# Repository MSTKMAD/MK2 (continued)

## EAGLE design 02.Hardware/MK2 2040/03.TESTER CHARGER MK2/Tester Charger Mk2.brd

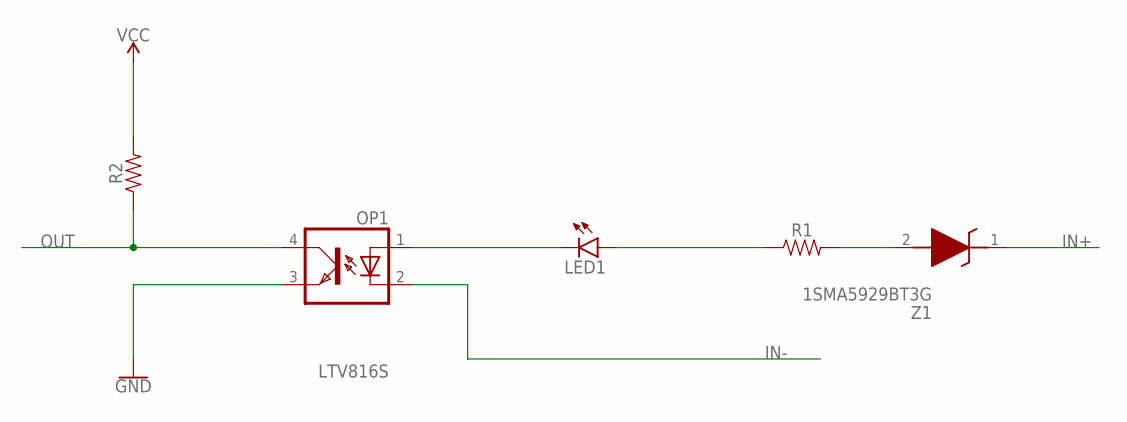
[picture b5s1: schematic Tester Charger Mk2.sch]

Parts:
LED1: LED3MM
OP1: LTV816S; SMD4
R1, R2: 0805
Z1: 1SMA5929BT3G; DIOM5226X220N

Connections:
GND: OP1.3 (EMIT)
IN+: Z1.1 (K)
IN-: OP1.2 (C)
unnamed: LED1.K (C), OP1.1 (A)
unnamed: R1.2, Z1.2 (A)
unnamed: LED1.A, R1.1
OUT: OP1.4 (COL), R2.1
VCC: R2.2

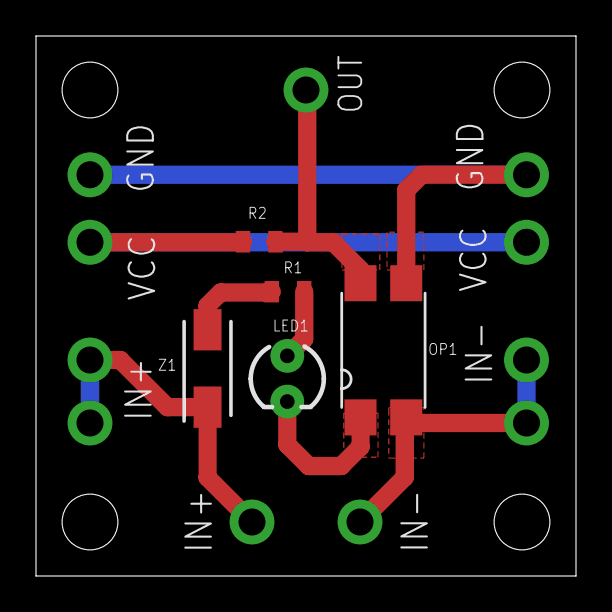
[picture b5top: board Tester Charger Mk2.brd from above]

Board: 2 copper layers, 30.0 x 30.0 mm, 5 parts (0 on the bottom side), 4 nets.

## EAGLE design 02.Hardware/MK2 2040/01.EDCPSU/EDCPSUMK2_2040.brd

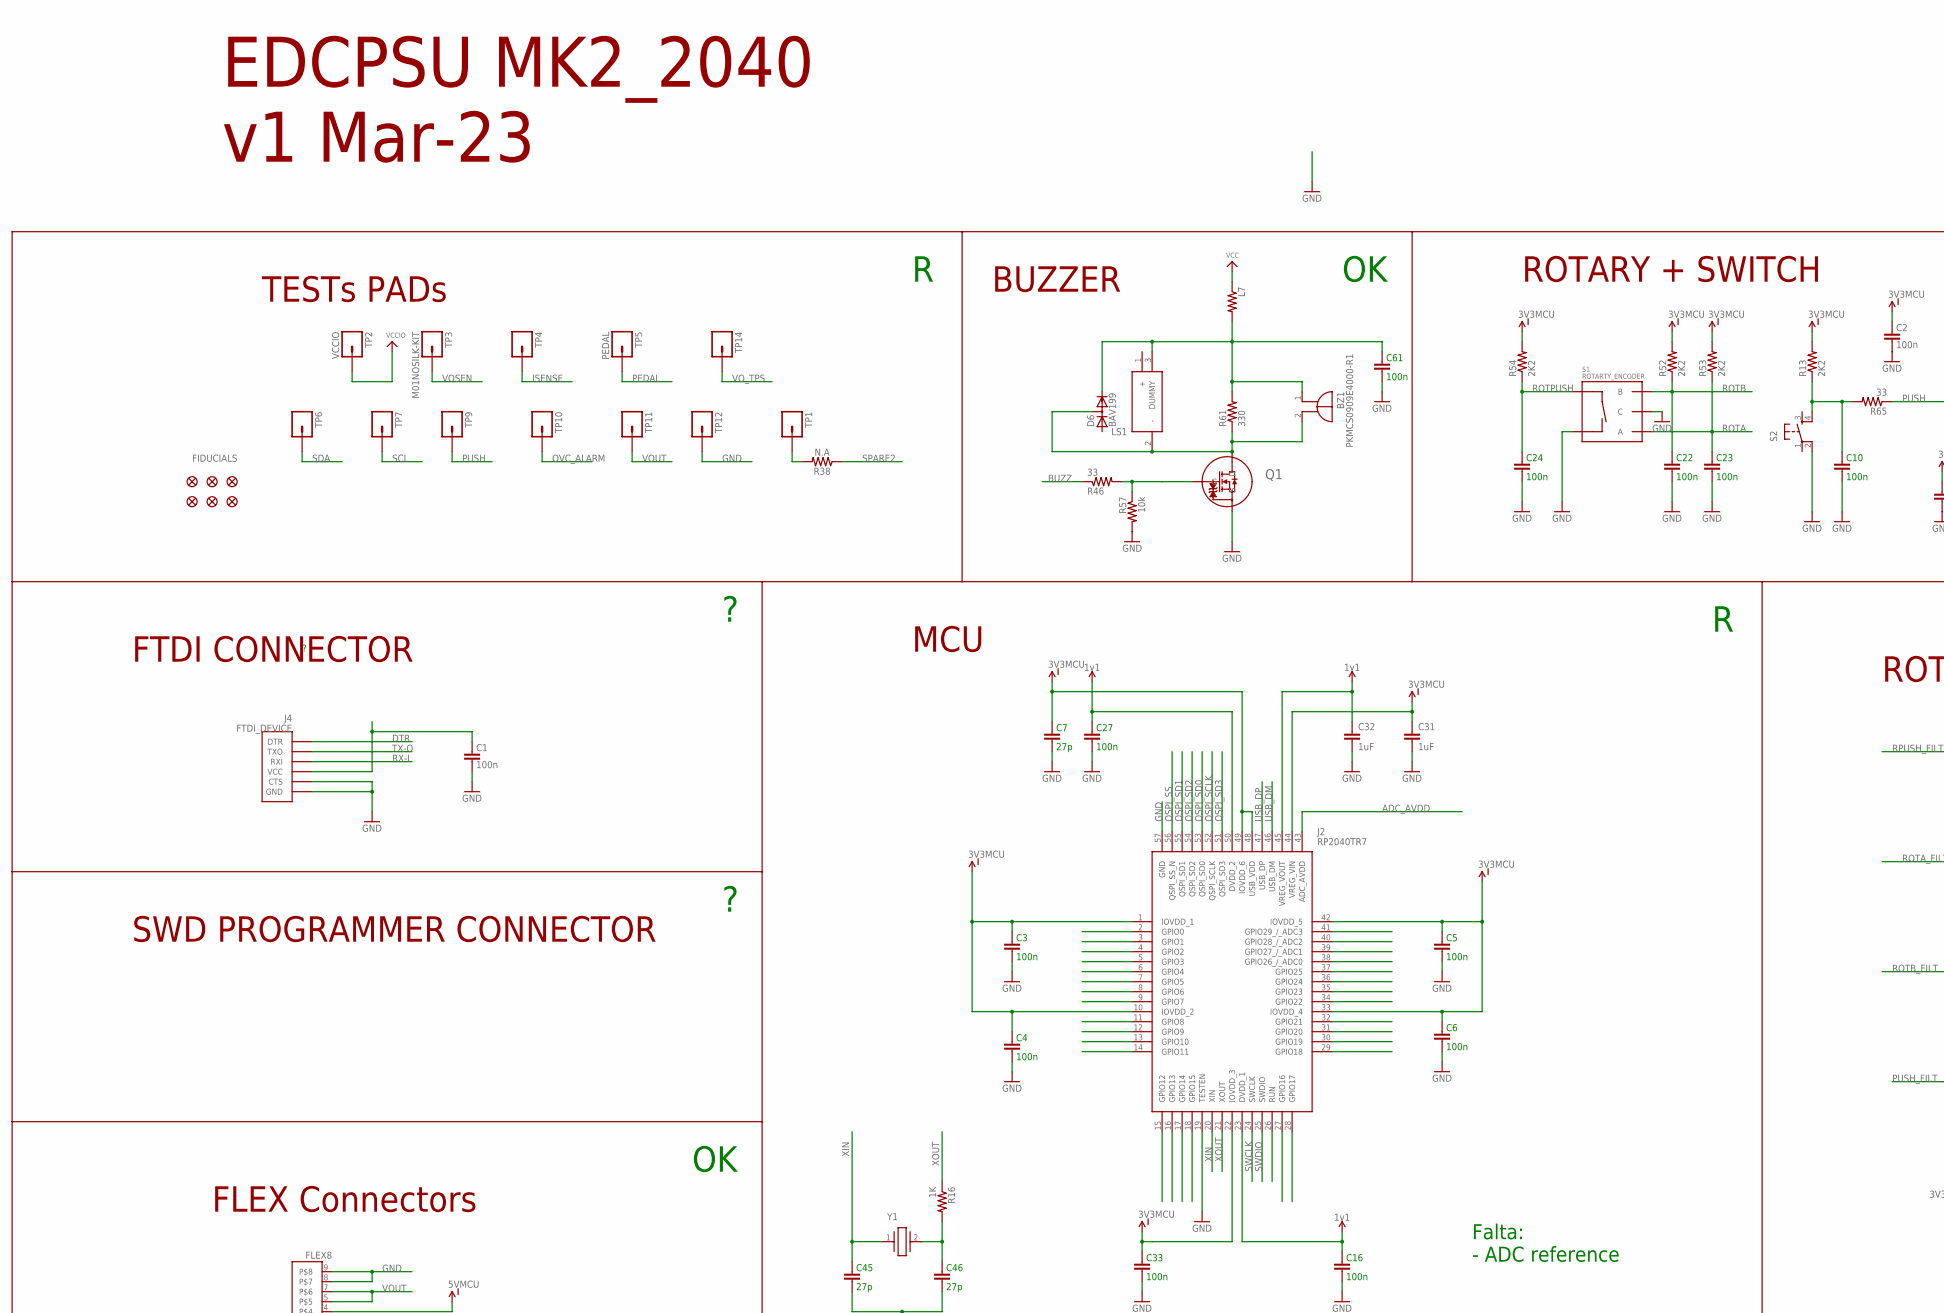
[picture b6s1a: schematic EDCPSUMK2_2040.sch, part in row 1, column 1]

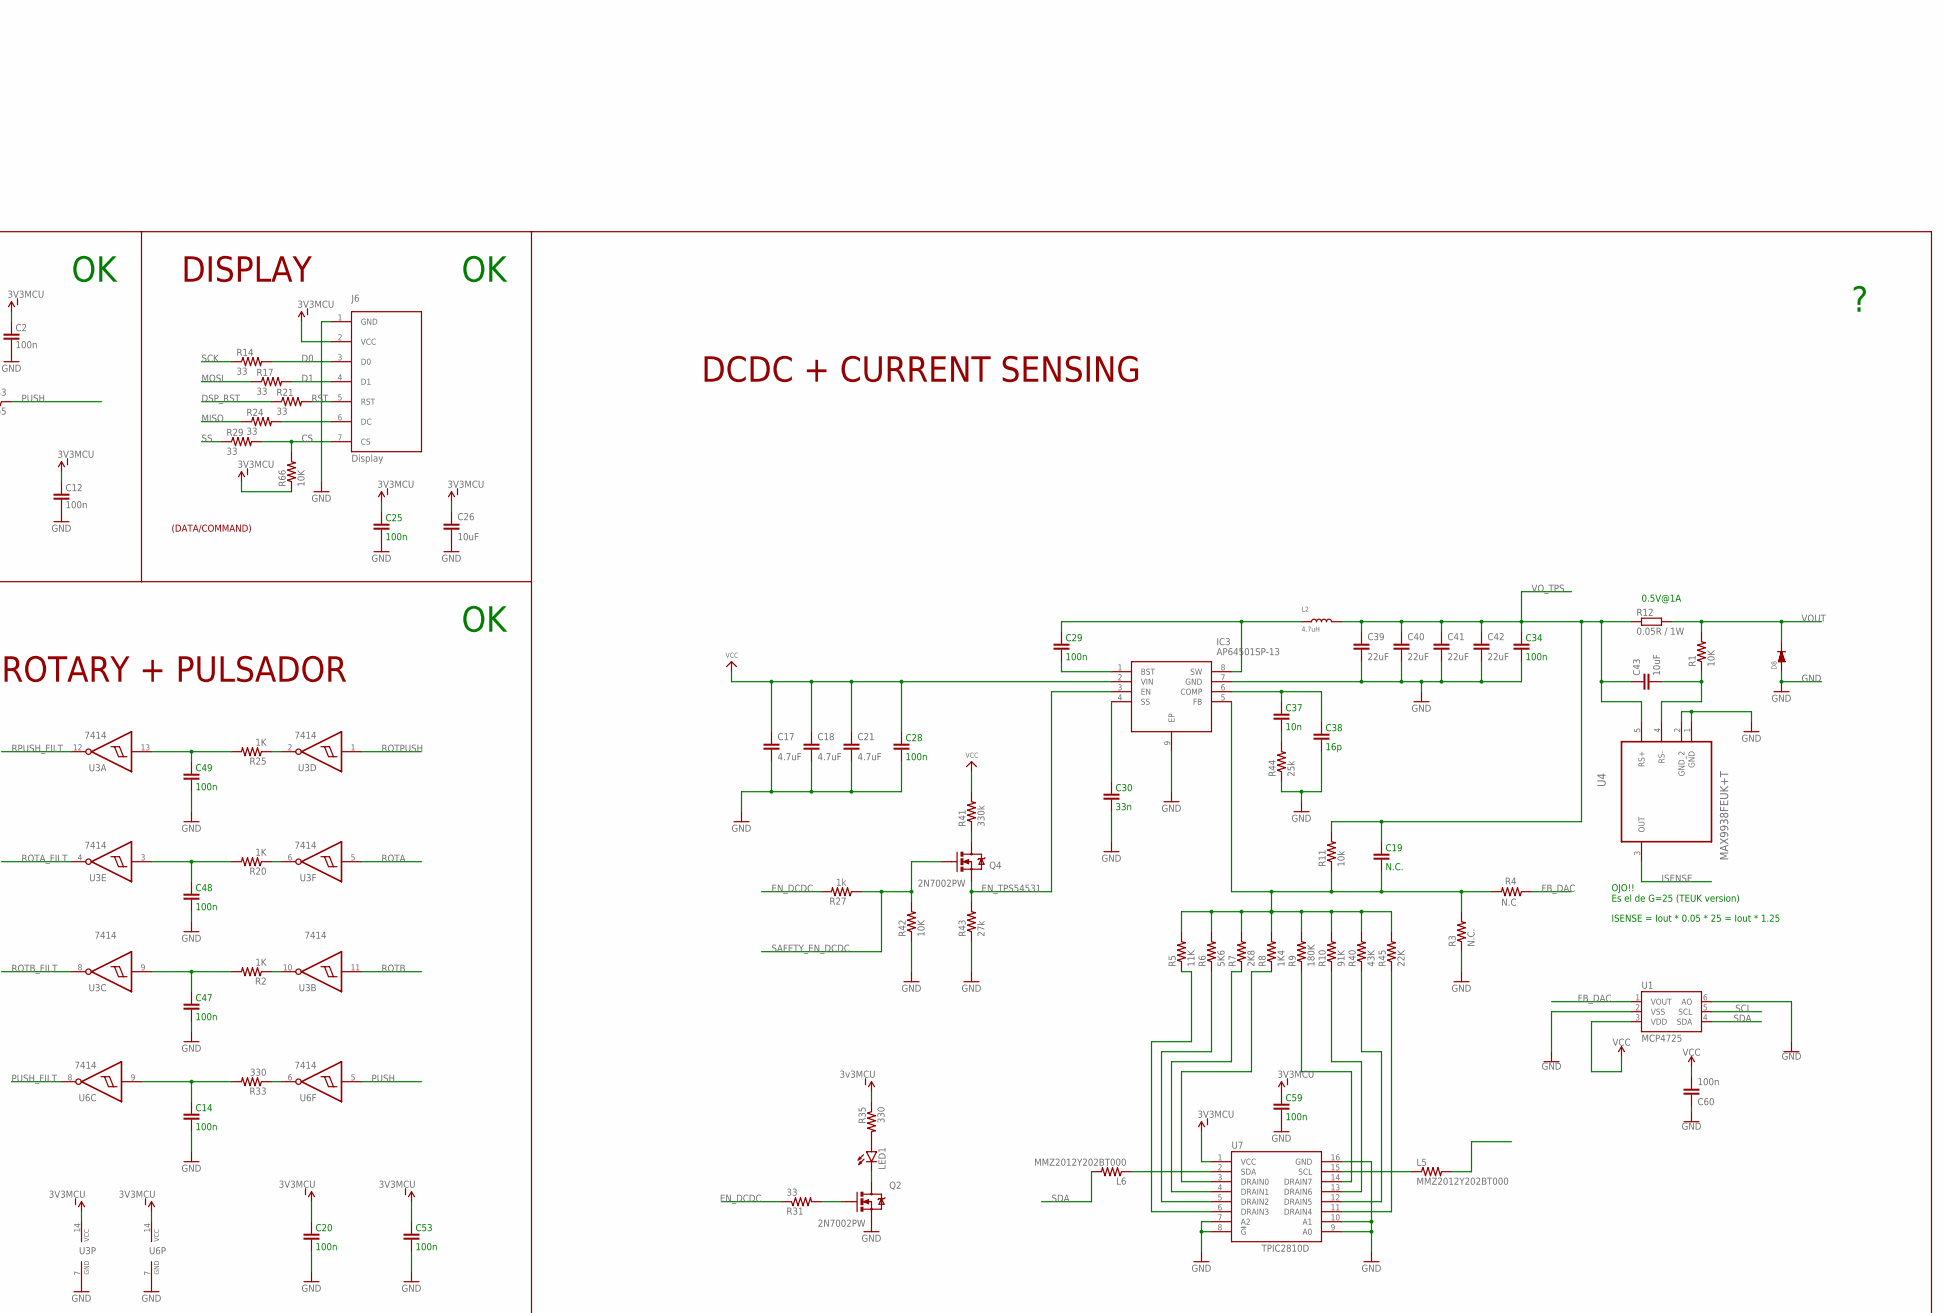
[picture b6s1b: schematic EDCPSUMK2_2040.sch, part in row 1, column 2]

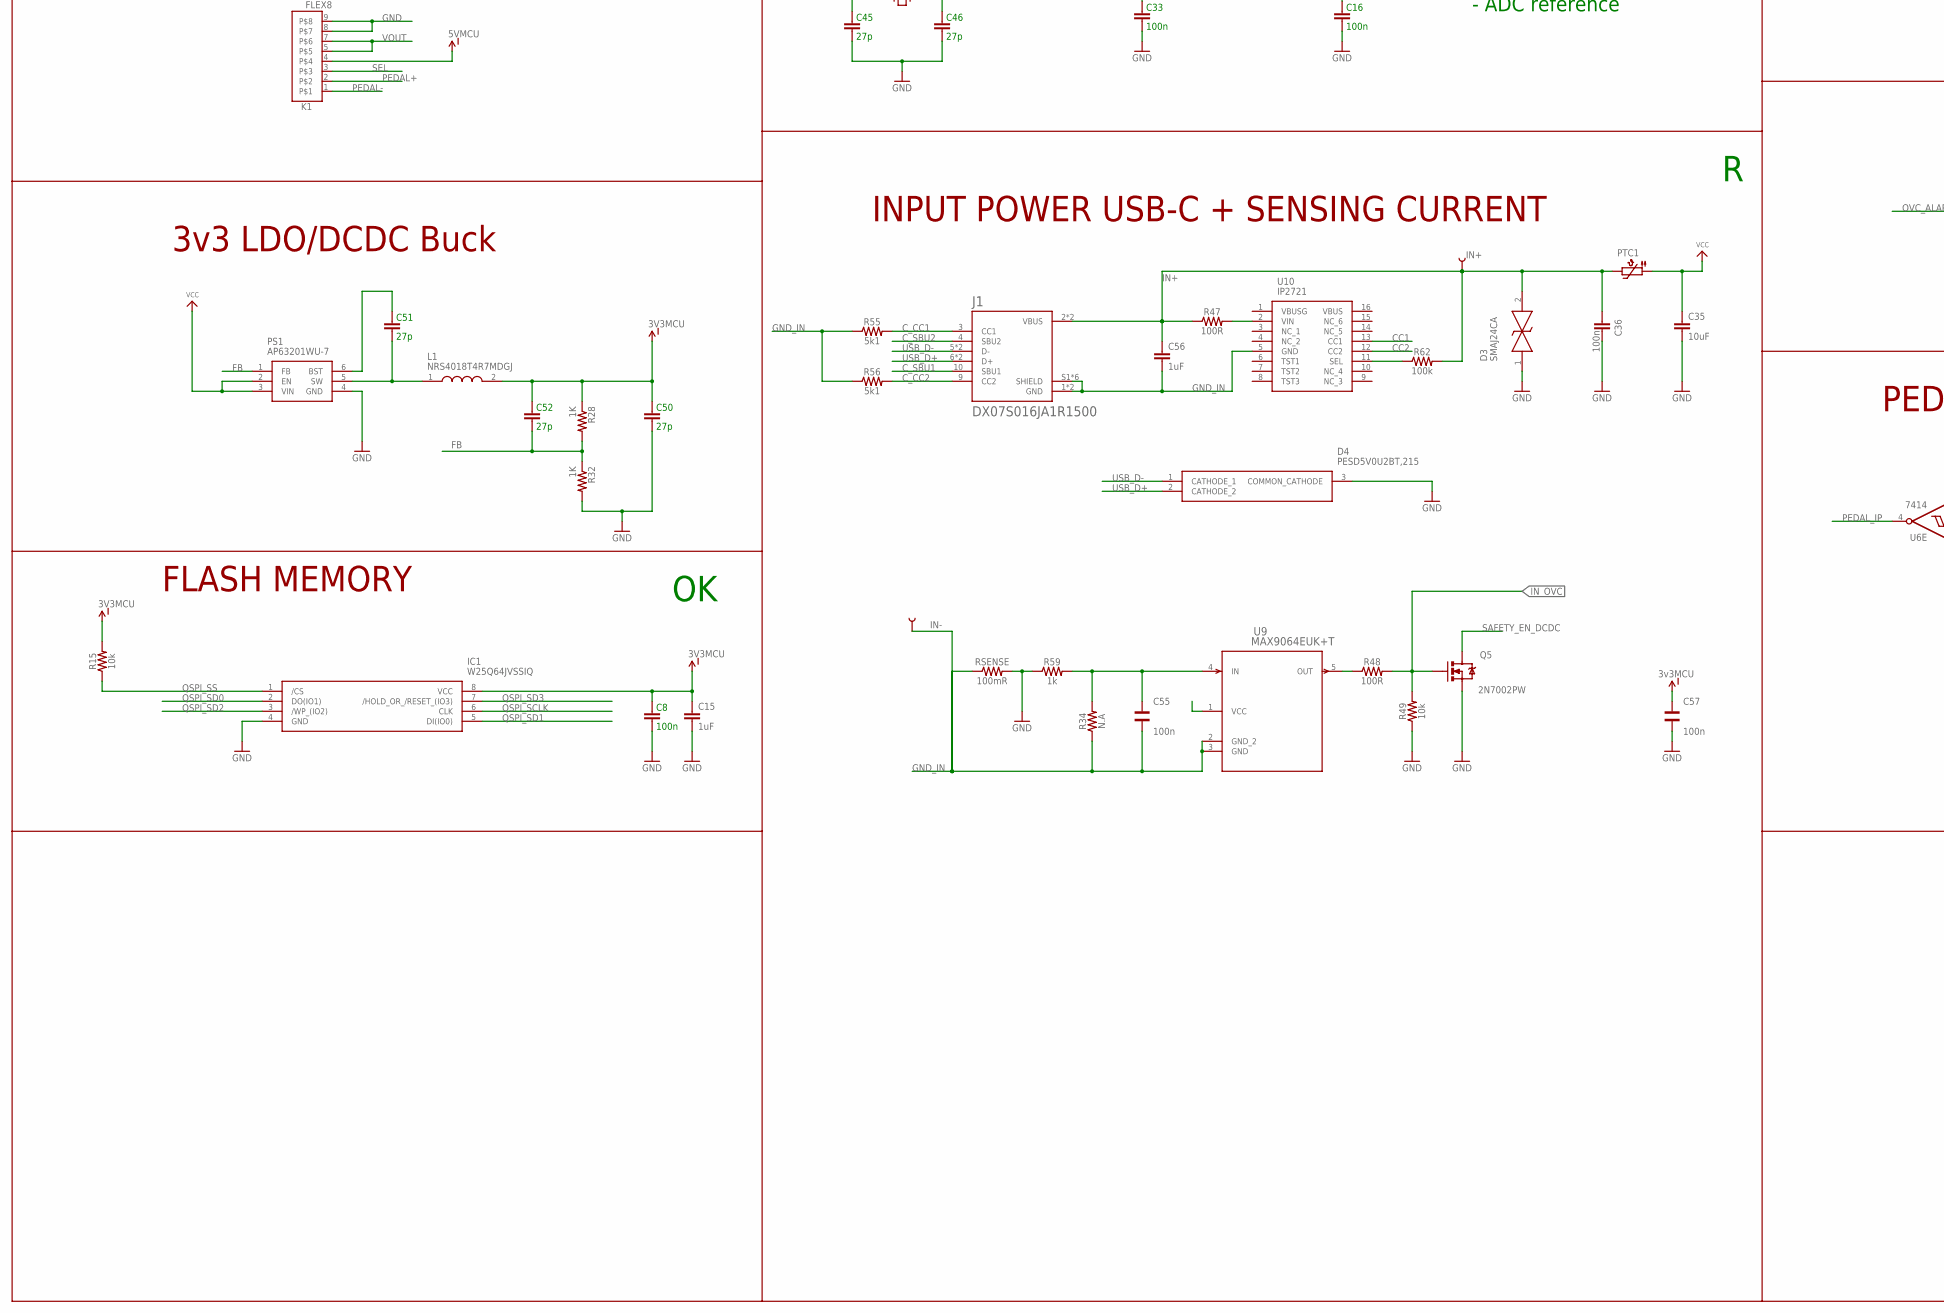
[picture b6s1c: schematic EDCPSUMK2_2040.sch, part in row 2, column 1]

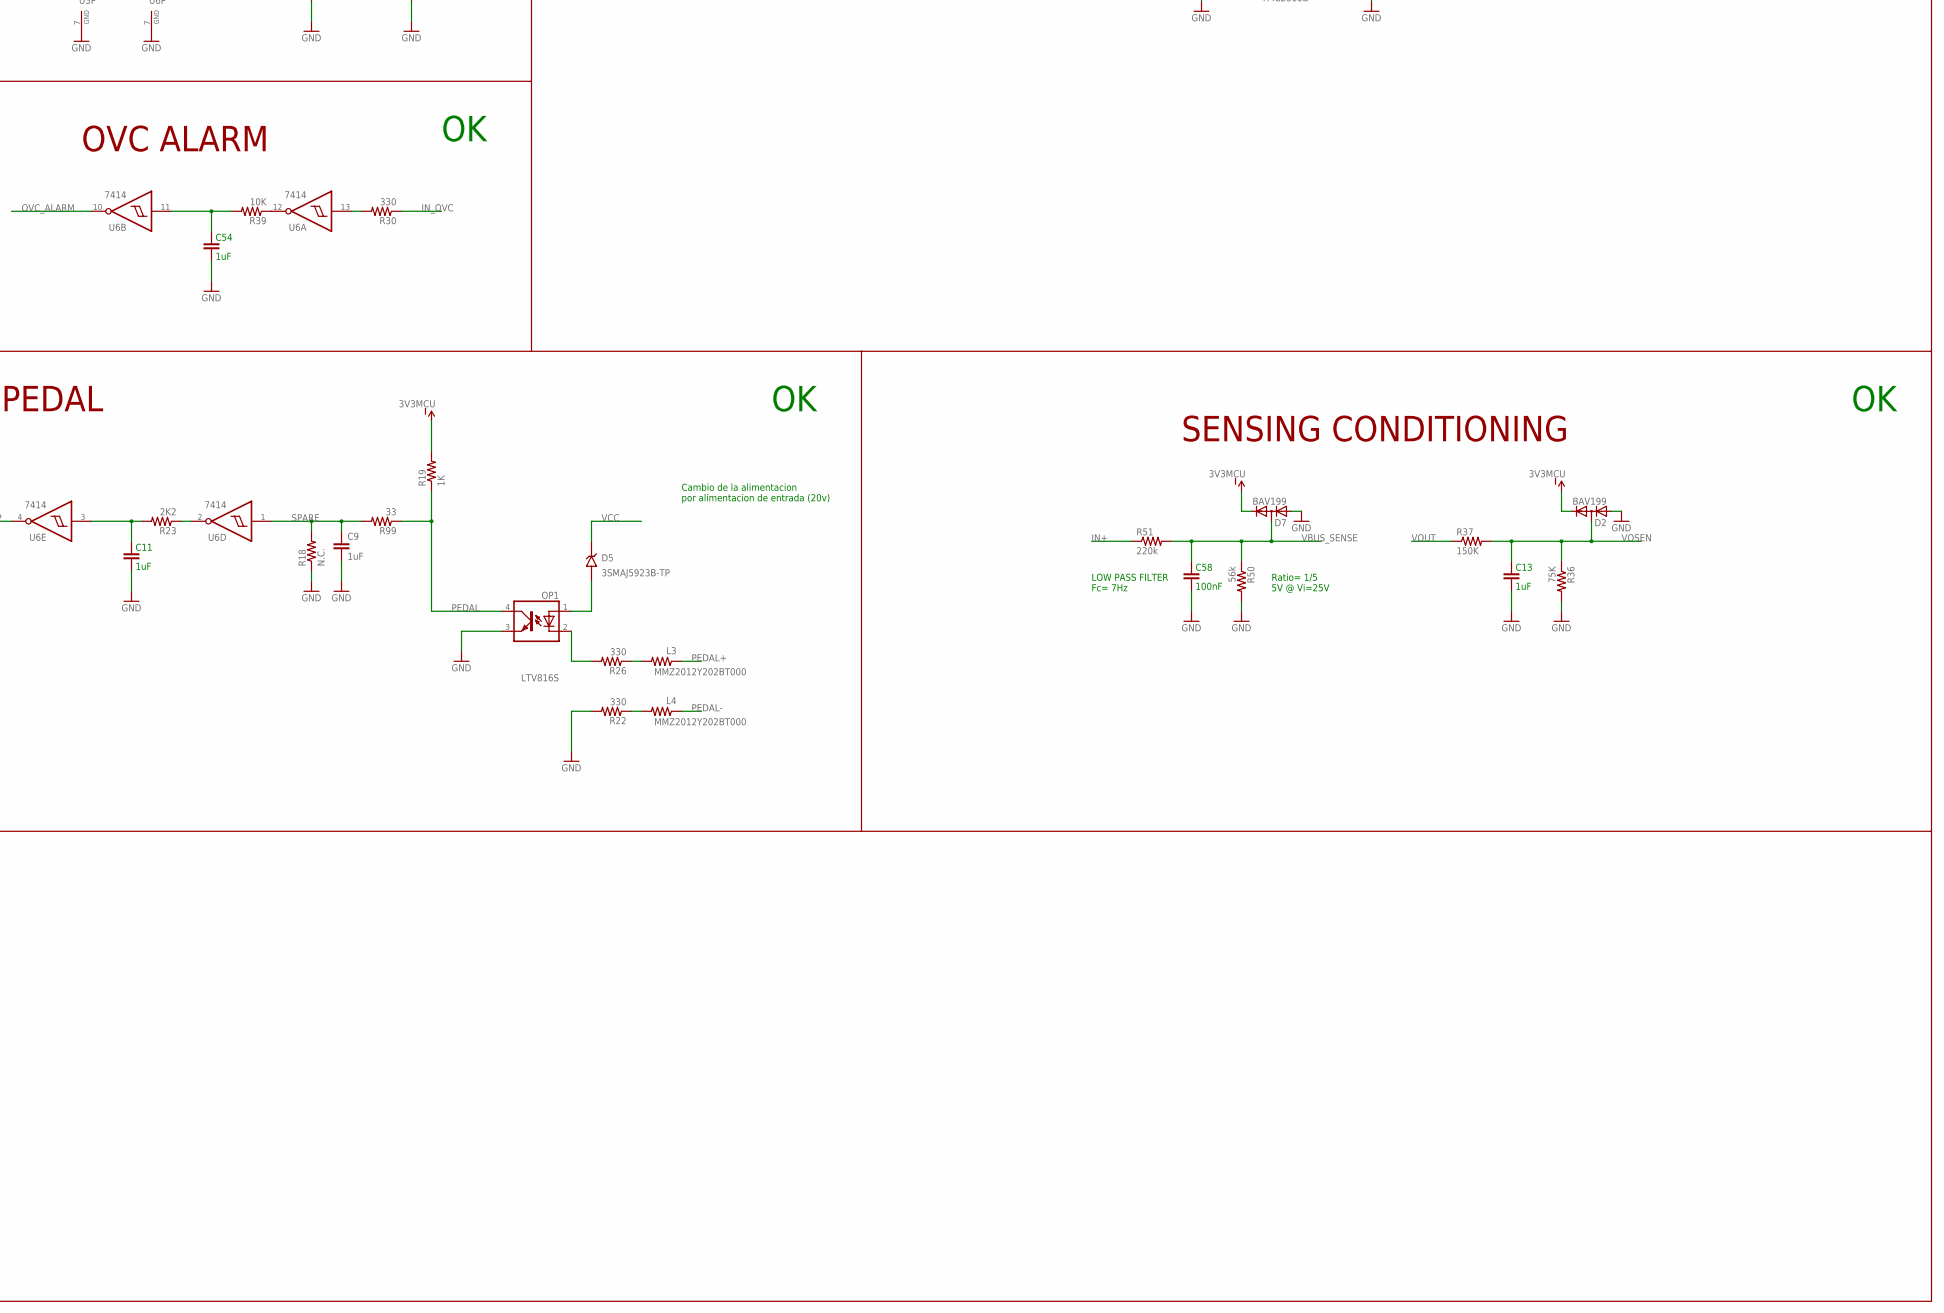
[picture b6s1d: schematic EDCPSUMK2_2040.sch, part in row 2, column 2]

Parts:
BZ1: PKMCS0909E4000-R1; PKMCS0909
C1, C2, C3, C4, C5, C6, C8, C10, C12, C14, C16, C20, C22, C23, C24, C25, C27, C28, C29, C33, C34, C36, C47, C48, C49, C53, C59, C61: 100n; 0805
C7, C45, C46, C50, C51, C52: 27p; 0805
C9, C15, C31, C32, C56: 1uF; 1206
C11, C13, C54: 1uF; 0805
C17, C18, C21: 4.7uF; 1210
C19: N.C.; 0805
C26, C35, C43: 10uF; 1206
C30: 33n; 0805
C37: 10n; 0805
C38: 16p; 0805
C39, C40, C41, C42: 22uF; 1210
C55, C57: 100n; WCAP-CSGP_1206
C58: 100nF; 0805
C60: 100n; C0805
D2, D6, D7: BAV199; SOT23
D3: SMAJ24CA; DIONM5127X229N
D4: PESD5V0U2BT,215; SOT95P230X110-3N
D5: 3SMAJ5923B-TP; DIOM4325X244N
D8: RB060M-60TR; SMADIODE
FID1, FID2, FID3, FID4, FID5, FID6: FIDUCIAL1X2; FIDUCIAL-1X2
IC1: W25Q64JVSSIQ; SOIC127P790X216-8N
IC3: AP64501SP-13; SOIC127P600X163-9N
IN+: TEST-POINT3; PAD.03X.03
IN-: TEST-POINT3; PAD.03X.03
J1: DX07S016JA1R1500; JAE_DX07S016JA1R1500
J2: RP2040TR7
J4: FTDI_DEVICE; FTDI_DEVICE_SIDE
J6: Display; OLED_LCD
K1: FLEX8
L1: NRS4018T4R7MDGJ; NRS4018T100MDGJ
L2: 4.7uH; WE-LHMI
L3, L4, L5, L6, L7: MMZ2012Y202BT000; 0805
LED1: LED3MM
LS1: SMT-0540-S-R; SMT0540SR
OP1: LTV816S; SMD4
PS1: AP63201WU-7; SOT95P280X100-6N
PTC1: 2A NOM / 3.5A LIM; 1812L
Q1: PJA3416AE_R1_00001; SOT23_PJA3416_PNJ
Q2, Q4, Q5: 2N7002PW; SOT323
R1, R39, R42, R66: 10K; 0805
R2, R16, R19, R20, R25, R28, R32: 1K; 0805
R3, R18: N.C.; 0805
R4: N.C; 0805
R5: 11K; 0805
R6: 5K6; 0805
R7: 2K8; 0805
R8: 1K4; 0805
R9: 180K; 0805
R10: 91K; 0805
R11, R57: 10k; 0805
R12: 0.05R / 1W; R2512
R13, R23, R52, R53, R54: 2K2; 0805
R14, R17, R21, R24, R29, R31, R46, R65, R99: 33; 0805
R15, R49: 10k; 0603
R22, R26: 330; 1206
R27: 1k; 0805
R30, R33, R35, R61: 330; 0805
R34, R38: N.A; 0603
R36: 75K; 0805
R37: 150K; 0805
R40: 43K; 0805
R41: 330k; 0805
R43: 27k; 0805
R44: 25k; 0805
R45: 22K; 0805
R47, R48: 100R; 0603
R50: 56k; 0603
R51: 220k; 0603
R55, R56: 5k1; 0603
R59: 1k; 0603
R62: 100k; 0603
RSENSE: 100mR; 1206
S1: ROTARTY_ENCODER; ROTARY_ENC_PLAIN
S2: TAC_SWITCH_KSC931G-SMD; TAC_SW_SMD_KSC931G
TP1, TP4, TP6, TP7, TP9, TP10, TP11, TP12, TP14: M01POGOPIN_HOLE_LARGE; 1X01_POGOPIN_HOLE_LARGE
TP2: VCCIO; 1X01_POGOPIN_HOLE_LARGE
TP3: M01NOSILK-KIT; 1X01NS-KIT
TP5: PEDAL; 1X01_POGOPIN_HOLE_LARGE
U1: MCP4725; SOT23-6
U3, U6: 7414; TSSOP14
U4: MAX9938FEUK+T; SOT95P280X145-5N
U7: TPIC2810D; SO16
U9: MAX9064EUK+T; 21-0057F_MXM
U10: IP2721; SOP65P640X120-16N
Y1: ABLS-12.000MHZ-B4-T; ABLS

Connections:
ADC_AVDD: J2.43 (ADC_AVDD)
BUZZ: R46.1
CC1: U10.13 (CC1)
CC2: U10.12 (CC2)
CS: J6.7 (CS), R29.2, R66.2
C_CC1: J1.3 (CC1), R55.2
C_CC2: J1.9 (CC2), R56.2
C_SBU1: J1.10 (SBU1)
C_SBU2: J1.4 (SBU2)
D0: J6.3 (D0), R14.2
D1: J6.4 (D1), R17.2
DSP_RST: R21.1
DTR: J4.P$1 (DTR)
EN_DCDC: R27.2, R31.1
EN_TPS54531: IC3.3 (EN), Q4.2 (S), R43.2
FB: C52.1, PS1.1 (FB), R28.2, R32.1
FB_DAC: R4.1, U1.1 (VOUT)
GND: C1.1, C2.1, C3.1, C4.1, C5.1, C6.1, C7.1, C8.1, C9.2, C10.1, C11.1, C12.1, C13.1, C14.1, C15.2, C16.1, C17.2, C18.2, C20.1, C21.2, C22.1, C23.1, C24.1, C25.1, C26.2, C27.1, C28.1, C30.1, C31.2, C32.2, C33.1, C34.1, C35.2, C36.1, C38.1, C39.2, C40.2, C41.2, C42.2, C45.1, C46.1, C47.1, C48.1, C49.1, C50.1, C53.1, C54.1, C57.1, C58.1, C59.1, C60.1, C61.1, D2.1 (A), D3.1, D4.3 (COMMON_CATHODE), D7.1 (A), D8.A, IC1.4 (GND), IC3.7 (GND), IC3.9 (EP), J2.19 (TESTEN), J2.57 (GND), J4.P$5 (CTS), J4.P$6 (GND), J6.1 (GND), K1.8, K1.9, OP1.3 (EMIT), PS1.4 (GND), Q1.2 (S), Q2.2 (S), Q5.2 (S), R3.1, R18.1, R22.2, R32.2, R36.2, R42.1, R43.1, R44.1, R49.1, R50.2, R57.2, R59.1, RSENSE.2, S1.C, S1.SW-, S2.2, TP12.1, U1.2 (VSS), U1.6 (AO), U3.7 (GND), U4.1 (GND), U4.2 (GND_2), U6.7 (GND), U7.7 (A2), U7.8 (!G), U7.9 (A0), U7.10 (A1), U7.16 (GND); also elsewhere on the board
GND_IN: C55.1, C56.2, IN-.P$1, J1.1 (GND), J1.12 (GND), J1.S1 (SHIELD), J1.S2 (SHIELD), J1.S3 (SHIELD), J1.S4 (SHIELD), J1.S5 (SHIELD), J1.S6 (SHIELD), R34.1, R55.1, R56.1, RSENSE.1, U9.2 (GND_2), U9.3 (GND), U10.5 (GND)
IN+: C36.2, C56.1, D3.2, IN+.P$1, J1.2 (VBUS), J1.11 (VBUS), PTC1.2, R47.1, R51.1, R62.2
ISENSE: TP4.1, U4.3 (OUT)
MISO: R24.1
MOSI: R17.1
unnamed: R5.1, U7.6 (DRAIN3)
unnamed: R6.1, U7.5 (DRAIN2)
unnamed: R7.1, U7.4 (DRAIN1)
unnamed: R8.1, U7.3 (DRAIN0)
unnamed: J6.6 (DC), R24.2
unnamed: R9.1, U7.14 (DRAIN7)
unnamed: R10.1, U7.13 (DRAIN6)
unnamed: R40.1, U7.12 (DRAIN5)
unnamed: C43.2, R1.1, U4.4 (RS-)
unnamed: LED1.A, R35.2
unnamed: LED1.K (C), Q2.3 (D)
unnamed: R33.1, U6.6 (O)
unnamed 35: R30.2, U6.13 (I); also elsewhere on the board
unnamed: R39.1, U6.12 (O)
unnamed: R45.1, U7.11 (DRAIN4)
unnamed: C10.2, R13.1, R65.2, S2.4
unnamed: C47.2, R2.2, U3.9 (I)
unnamed: D5.A, OP1.1 (A)
unnamed: Q2.1 (G), R31.2
unnamed: R2.1, U3.10 (O)
unnamed: R20.1, U3.6 (O)
unnamed: R25.1, U3.2 (O)
unnamed: C49.2, R25.2, U3.13 (I)
unnamed: C48.2, R20.2, U3.3 (I)
unnamed: C11.2, R23.2, U6.3 (I)
unnamed: C1.2, J4.P$4 (VCC)
unnamed: R23.1, U6.2 (O)
unnamed: Q4.3 (D), R41.1
unnamed: C14.2, R33.2, U6.9 (I)
unnamed: R38.2, TP1.1
unnamed: C54.2, R39.2, U6.11 (I)
unnamed: L6.1, U7.2 (SDA)
unnamed: OP1.2 (C), R26.2
unnamed: L3.2, R26.1
unnamed: C30.2, IC3.4 (SS)
unnamed: R62.1, U10.11 (SEL)
unnamed: L4.2, R22.1
unnamed: C29.1, IC3.1 (BST)
unnamed: C19.1, IC3.5 (FB), R3.2, R4.2, R5.2, R6.2, R7.2, R8.2, R9.2, R10.2, R11.1, R40.2, R45.2
unnamed: R47.2, U10.2 (VIN)
unnamed: C29.2, IC3.8 (SW), L2.1
unnamed: C37.2, C38.2, IC3.6 (COMP)
unnamed: C37.1, R44.2
unnamed: L5.1, U7.15 (SCL)
unnamed: C51.2, PS1.6 (BST)
unnamed: R48.1, U9.5 (OUT)
unnamed: C55.2, R34.2, R59.2, U9.4 (IN)
unnamed: C46.2, R16.2, Y1.2
unnamed: Q1.1 (G), R46.2, R57.1
unnamed: BZ1.2 (-), D6.3 (AC), LS1.2 (-), Q1.3 (D), R61.1
unnamed: C51.1, L1.1, PS1.5 (SW)
PEDAL: OP1.4 (COL), R19.1, R99.1, TP5.1
PEDAL+: K1.2, L3.1
PEDAL-: K1.1, L4.1
PEDAL_IP: U6.4 (O)
PUSH: R65.1, TP9.1, U6.5 (I)
PUSH_FILT: U6.8 (O)
QSPI_SCLK: IC1.6 (CLK), J2.52 (QSPI_SCLK)
QSPI_SD0: IC1.2 (DO(IO1)), J2.53 (QSPI_SD0)
QSPI_SD1: IC1.5 (DI(IO0)), J2.55 (QSPI_SD1)
QSPI_SD2: IC1.3 (/WP_(IO2)), J2.54 (QSPI_SD2)
QSPI_SD3: IC1.7 (/HOLD_OR_/RESET_(IO3)), J2.51 (QSPI_SD3)
QSPI_SS: IC1.1 (/CS), J2.56 (QSPI_SS_N), R15.1
ROTA: C23.2, R53.1, S1.A, U3.5 (I)
ROTA_FILT: U3.4 (O)
ROTB: C22.2, R52.1, S1.B, U3.11 (I)
ROTB_FILT: U3.8 (O)
ROTPUSH: C24.2, R54.1, S1.SW+, U3.1 (I)
RPUSH_FILT: U3.12 (O)
RST: J6.5 (RST), R21.2
RX-I: J4.P$3 (RXI)
SAFETY_EN_DCDC: Q4.1 (G), Q5.3 (D), R27.1, R42.2
SCK: R14.1
SCL: TP7.1, U1.5 (SCL)
SCL1: L5.2
SDA: L6.2, TP6.1, U1.4 (SDA)
SEL: K1.3
SPARE: C9.1, R18.2, R99.2, U6.1 (I)
SPARE2: R38.1
SS: R29.1
SWCLK: J2.24 (SWCLK)
SWDIO: J2.25 (SWDIO)
TX-O: J4.P$2 (TXO)
USB_D+: D4.2 (CATHODE_2), J1.6 (D+), J1.7 (D+)
USB_D-: D4.1 (CATHODE_1), J1.5 (D-), J1.8 (D-)
USB_DM: J2.46 (USB_DM)
USB_DP: J2.47 (USB_DP)
VBUS_SENSE: C58.2, D7.3 (AC), R50.1, R51.2
VCC: C17.1, C18.1, C21.1, C28.2, C35.1, C60.2, D5.C (K), IC3.2 (VIN), L7.1, PS1.2 (EN), PS1.3 (VIN), PTC1.1, R41.2, U1.3 (VDD); also elsewhere on the board
VCC-ISO: C2.2, C3.2, C4.2, C5.2, C6.2, C7.2, C8.2, C12.2, C15.1, C20.2, C25.2, C26.1, C31.1, C33.2, C50.2, C52.2, C53.2, C57.2, C59.2, D2.2 (C), D7.2 (C), IC1.8 (VCC), J2.1 (IOVDD_1), J2.10 (IOVDD_2), J2.22 (IOVDD_3), J2.33 (IOVDD_4), J2.42 (IOVDD_5), J2.44 (VREG_VIN), J2.48 (USB_VDD), J2.49 (IOVDD_6), J6.2 (VCC), K1.4, L1.2, R13.2, R15.2, R19.2, R28.1, R35.1, R52.2, R53.2, R54.2, R66.1, U3.14 (VCC), U6.14 (VCC), U7.1 (VCC); also elsewhere on the board
VCCA: C16.2, C27.2, C32.1, J2.23 (DVDD_1), J2.45 (VREG_VOUT), J2.50 (DVDD_2)
VCCIO: TP2.1
VIN_ALARM: TP10.1, U6.10 (O)
VOSEN: C13.2, D2.3 (AC), R36.1, R37.2, TP3.1
VOUT: D8.C (K), K1.5, K1.7, R1.2, R12.2, R37.1, TP11.1
VO_TPS: C19.2, C34.2, C39.1, C40.1, C41.1, C42.1, C43.1, L2.2, R11.2, R12.1, TP14.1, U4.5 (RS+)
XIN: C45.2, J2.20 (XIN), Y1.1
XOUT: J2.21 (XOUT), R16.1

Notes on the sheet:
0.5V@1A
SENSING CONDITIONING
MCU
EDCPSU MK2_2040 v1 Mar-23
(DATA/COMMAND)
BUZZER
ROTARY + SWITCH
DISPLAY
FIDUCIALS
OJO!! Es el de G=25 (TEUK version)
ISENSE = Iout * 0.05 * 25 = Iout * 1.25
FLEX Connectors
Ratio= 1/5 5V @ Vi=25V
LOW PASS FILTER Fc= 7Hz
PEDAL
ROTARY + PULSADOR
OVC ALARM
DCDC + CURRENT SENSING
3v3 LDO/DCDC Buck
TESTs PADs
INPUT POWER USB-C + SENSING CURRENT
FTDI CONNECTOR
SWD PROGRAMMER CONNECTOR
Cambio de la alimentacion por alimentacion de entrada (20v)
Falta: - ADC reference
FLASH MEMORY

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
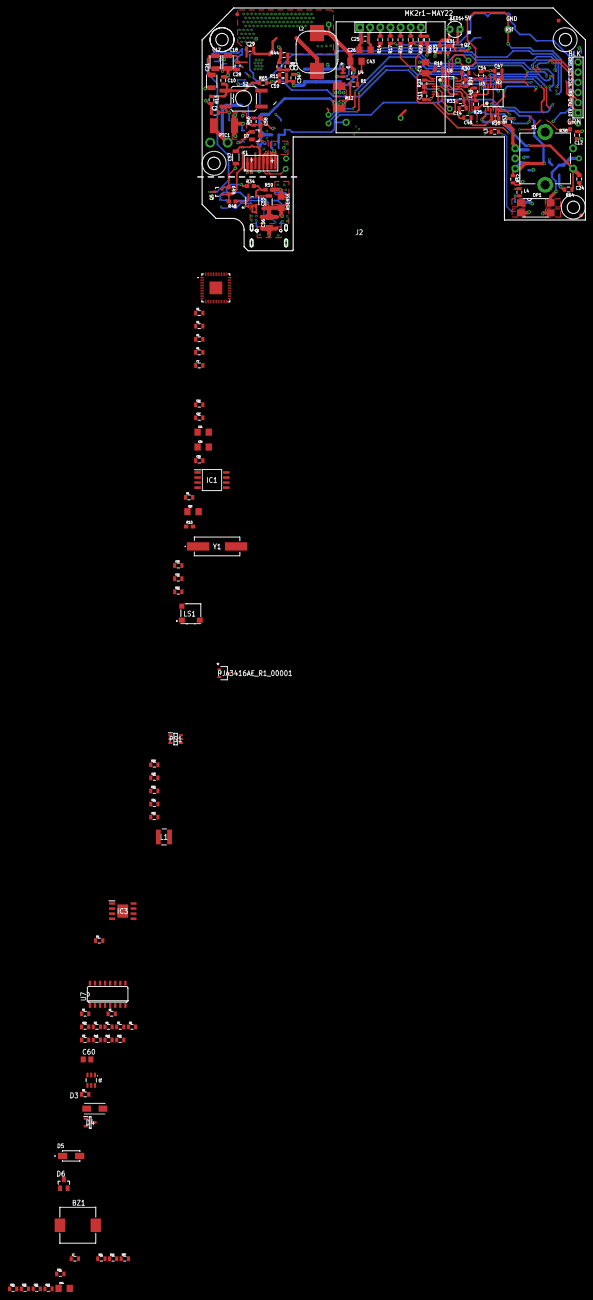
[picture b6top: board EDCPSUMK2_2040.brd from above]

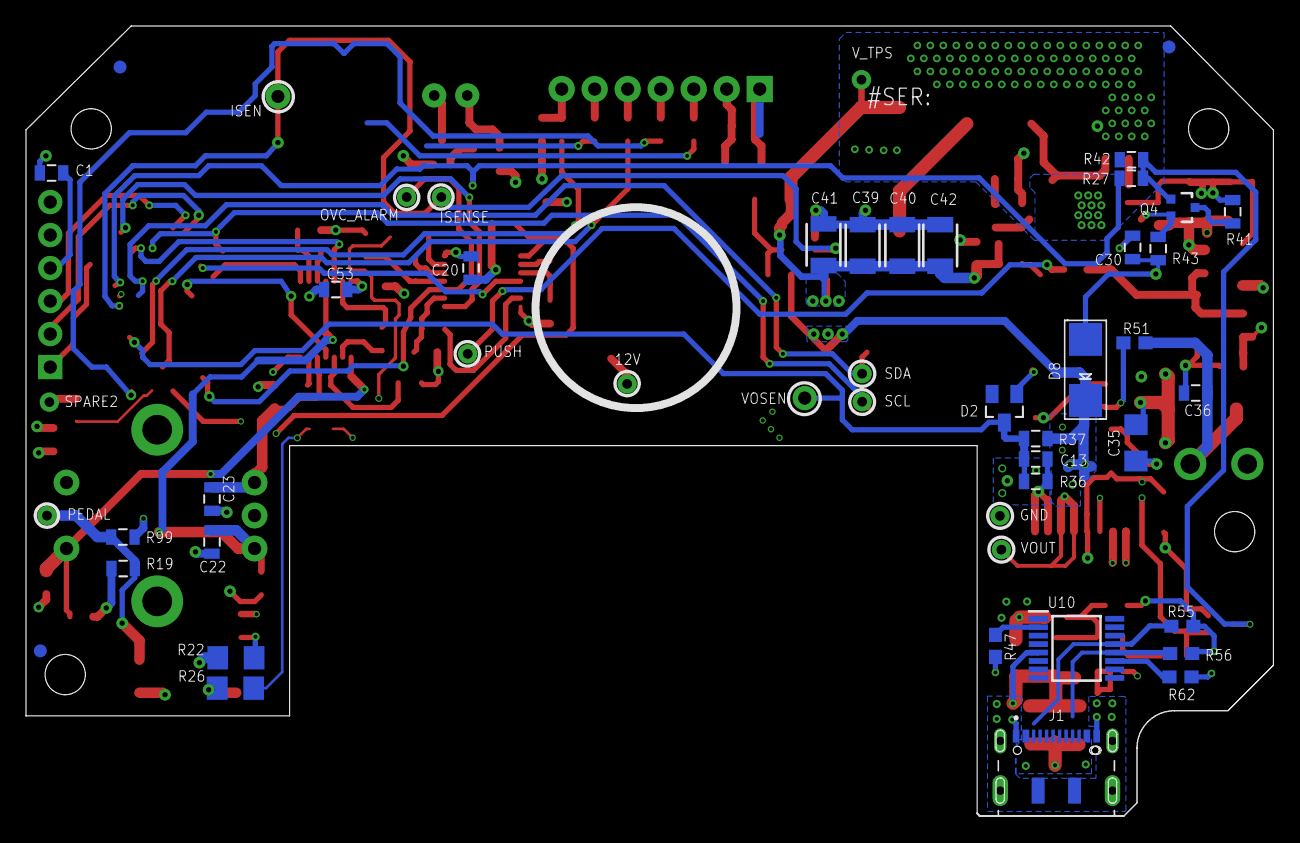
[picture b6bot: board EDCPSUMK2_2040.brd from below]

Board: 4 copper layers, 96.0 x 60.8 mm, 190 parts (36 on the bottom side), 97 nets.

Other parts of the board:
C44: 10uF; 1206
C62: 22u 10V X5R; 0805
C63, C64: 4.7u 50V X5R; 0805
R58: 330; 0805

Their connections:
GND: C44.2, C62.1, C63.1, C64.1, R58.2; also elsewhere on the board
unnamed 35: R58.1; also elsewhere on the board
VCC: C63.2, C64.2; also elsewhere on the board
VCC-ISO: C62.2; also elsewhere on the board

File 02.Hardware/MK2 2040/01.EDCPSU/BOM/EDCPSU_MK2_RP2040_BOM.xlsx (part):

|  |  |  |  |  |  |  |  | BOM VERSION v1
 |  |  |  |  |  |  |  |  | 45058
 |  |  |  |  |  |  |  |  | MK2r2-RP2040
Pos | Assembly? | Es IGUAL respecto MK2? | SETI Compra YA | USB-C DUAL-USBC | Qty | Parts | Value | Device | Package | Description | Details | DIGIKEY | COST (500pcs)
2 | P | IGUAL | P | MK1-JACK | 1 | BZ1 | PKMCS0909E4000-R1 | PKMCS0909E4000-R1 | PKMCS0909 | PKMCS0909E4000-R1 |  | https://www.digikey.es/es/products/detail/murata-electronics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
3 | P | IGUAL | P | MK1-JACK | 3 | C17, C18, C21 | 4.7uF 50V X7R | CAP1210 | 1210 | Capacitor
4 | NO | NO SE MONTA | NO SE MONTA | MK1-JACK | 2 | C19, C65 | N.C. | CAP0805 | 805 | Capacitor
5 | P | IGUAL | P | MK1-JACK | 34 | C2, C4, C5, C6, C7, C8, C10, C12, C14, C16, C20, C22, C23, C24, C25, C27, C28, 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 | 100n 50v X7R/X5R | CAP0805 | 805 | Capacitor
6 | P | IGUAL | P | MK1-JACK | 4 | C26, C35, C43, C51 | 10uF 50V X5R/X7R | CAP1206 | 1206 | Capacitor
7 | P | IGUAL | P | MK1-JACK | 2 | C3, C62 | 22uF 10V X5R | CAP0805 | 805 | Capacitor
8 | P | IGUAL | P | MK1-JACK | 1 | C30 | 33n | CAP0805 | 805 | Capacitor
9 | P | IGUAL | P | MK1-JACK | 1 | C37 | 10nF | CAP0805 | 805 | Capacitor
10 | P | IGUAL | P | MK1-JACK | 1 | C38 | 16pF | CAP0805 | 805 | Capacitor
11 | P | IGUAL | P | MK1-JACK | 4 | C39, C40, C41, C42 | 22uF 25V X5R | CAP1210 | 1210 | Capacitor
12 | NO | NO SE MONTA | NO SE MONTA | MK1-JACK | 1 | C52 | N.C | CAP0805 | 805 | Capacitor
13 | P | IGUAL | P | MK1-JACK | 2 | C59, C61 | 27p | CAP0805 | 805 | Capacitor
14 | P | IGUAL | P | MK1-JACK | 2 | C63, C64 | 4.7uF 50V X5R | CAP0805 | 805 | Capacitor
15 | P | IGUAL | P | MK1-JACK | 8 | C9, C11, C13, C15, C45, C46, C54, C56 | 1uF 50V X7R | CAP0805 | 805 | Capacitor
16 | P | NUEVO | ESPERAR | DUAL-USBC | 1 | D1 | SMAJ24CA | SMAJ24CA | DIONM5127X229N | ESD Suppressors / TVS Diodes 24volts 5uA 10.3 Amps Bi-Dir
17 | P | IGUAL | P | MK1-JACK | 3 | D2, D3, D7 | BAV199 | BAV199 | SOT23 | DIODE |  | https://www.digikey.es/es/products/detail/infineon-technolog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
18 | P | NUEVO | P | DUAL-USBC | 1 | D4 | PESD5V0U2BT,215 | PESD5V0U2BT,215 | SOT95P230X110-3N | PESD5V0U2BT - Ultra low capacitance bidirectional double ESD protection diode
19 | P | NUEVO | ESPERAR | MK1-JACK | 1 | D5 | 3SMAJ5923B-TP | 3SMAJ5923B-TP | DIOM5226X244N | Zener Diodes 3W 8.2V
20 | NO | NO SE MONTA | NO SE MONTA | MK1-JACK | 1 | D6 | N.C | DSMC | DO-214AB
21 | P | IGUAL | P | MK1-JACK | 1 | D8 | RB060M-60TR | 3SMAJ5923B-TP | SOD123-F | Zener Diodes 3W 8.2V |  | https://www.digikey.es/es/products/detail/rohm-semiconductor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
22 | P | NUEVO | P | MK1-JACK | 1 | DZ1 | MMSZ5227B-7-F | MMSZ5227B-7-F | SOD123 | Diode Zener 3.6V 5% 500mW 2Pin SOD123 Diodes Inc MMSZ5227B-7-F Zener Diode, 3.6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 |  | https://www.digikey.es/es/products/detail/diodes-incorporate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
25 | P | IGUAL | P | DUAL-USBC | 1 | J1 | DX07S016JA1R1500 | DX07S016JA1R1500 | JAE_DX07S016JA1R1500 | USB-C (USB TYPE-C) USB 2.0 Receptacle Connector 24 (16+8 Dummy) Position Surfac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 |  | https://www.digikey.es/es/products/detail/jae-electronics/DX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
26 | P | IGUAL | P | MK1-JACK | 1 | J6 | Display | OLED_LCD | OLED_LCD
27 | P | NUEVO | ESPERAR | MK1-JACK | 1 | JP1 | 20021521-00010T1LF | 20021521-00010T1LF | 20021521-00010T1LF | MINITEK 127 SHROUDED HDR
28 | P | IGUAL | P | MK1-JACK | 1 | K1 | FLEX CONNECTORES | FLEX8 | FLEX8 | WR-FPC 1mm SMT Horiz. Bot. Contact Hinge type WR-FPC 1mm 08 pins Hinge type SMT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
29 | P | NUEVO | ESPERAR | MK1-JACK | 1 | L1 | NRS4018T4R7MDGJ | NRS4018T4R7MDGJ | NRS4018T100MDGJ | Inductor SMD wirewound 4.7uH
30 | P | NUEVO | P | MK1-JACK | 1 | L2 | INDUCTOR 4.7uH 15mR | PA4342.472NLT | 11.5x10.3 | Inductor SMD wirewound 4.7uH 15mR 10A |  | https://www.digikey.es/en/products/detail/pulse-electronics/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
31 | P | IGUAL | P | MK1-JACK | 5 | L3, L4, L5, L6, L7 | MMZ2012Y202BT000 | RESISTOR0805-RES | 805 | Resistor |  | https://www.digikey.es/es/products/detail/tdk-corporation/MM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
32 | P | IGUAL | P | MK1-JACK | 1 | LED1 |  | LED3MM | LED3MM | LEDs
33 | NO | NO SE MONTA | NO SE MONTA | MK1-JACK | 1 | LS1 | SMT-0540-S-R | SMT-0540-S-R | SMT0540SR | Speakers & Transducers SMD TRANSDUCER 3VP-P 100MA
34 | P | IGUAL | P | MK1-JACK | 1 | OP1 | LTV816S | LTV816S | SMD4 | OPTO COUPLER |  | https://www.digikey.es/es/products/detail/liteon/LTV-816S/38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
35 | P | NUEVO | P | MK1-JACK | 1 | PTC1 | 2A NOM / 3.5A LIM | PTC- | 1812L | Positive Temperature Coefficient Resistor (PTC)
36 | P | IGUAL | P | MK1-JACK | 4 | Q2, Q4, Q5, Q9 | 2N7002PW | MOSFET-NCHANNEL2N7002PW | SOT323 | Common NMOSFET Parts |  | https://www.digikey.es/es/products/detail/nexperia-usa-inc/2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
37 | P | IGUAL | P | MK1-JACK | 8 | R1, R11, R32, R39, R40, R42, R49, R66 | 10K | RESISTOR0805 | 805 | Generic Resistor Package
38 | P | IGUAL | P | MK1-JACK | 1 | R10 | 22K | RESISTOR0805 | 805 | Generic Resistor Package
39 | P | IGUAL | P | MK1-JACK | 1 | R12 | 0.05R / 1W | RR2512 | R2512 | RESISTOR, European symbol
40 | P | IGUAL | P | MK1-JACK | 5 | R13, R23, R52, R53, R54 | 2K2 | RESISTOR0805 | 805 | Generic Resistor Package
41 | P | IGUAL | P | MK1-JACK | 7 | R14, R17, R21, R24, R28, R29, R65 | 33R | RESISTOR0805 | 805 | Generic Resistor Package
42 | NO | NO SE MONTA | NO SE MONTA | MK1-JACK | 8 | R15, R16, R18, R30, R34, R45, R58, R60 | N.C | RESISTOR0805 | 805 | Generic Resistor Package
43 | P | IGUAL | P | MK1-JACK | 7 | R2, R19, R20, R25, R27, R46, R59 | 1K | RESISTOR0805 | 805 | Generic Resistor Package
44 | P | IGUAL | P | MK1-JACK | 6 | R22, R26, R31, R33, R61, R99 | 330R | RESISTOR0805 | 805 | Generic Resistor Package
45 | P | IGUAL | P | MK1-JACK | 1 | R3 | 11K | RESISTOR0805 | 805 | Generic Resistor Package
46 | P | IGUAL | P | MK1-JACK | 1 | R37 | 150K | RESISTOR0805 | 805 | Generic Resistor Package
47 | P | IGUAL | P | MK1-JACK | 2 | R38, R63 | 27R | RESISTOR0805 | 805 | Generic Resistor Package
48 | P | IGUAL | P | MK1-JACK | 1 | R4 | 5K6 | RESISTOR0805 | 805 | Generic Resistor Package
49 | P | IGUAL | P | MK1-JACK | 1 | R41 | 330K | RESISTOR0805 | 805 | Generic Resistor Package
50 | P | IGUAL | P | MK1-JACK | 2 | R43,R36 | 27K | RESISTOR0805 | 805 | Generic Resistor Package
51 | P | IGUAL | P | MK1-JACK | 1 | R44 | 25K | RESISTOR0805 | 805 | Generic Resistor Package
52 | P | IGUAL | P | MK1-JACK | 2 | R47, R48 | 100R | RESISTOR0805 | 805 | Generic Resistor Package
53 | P | IGUAL | P | MK1-JACK | 1 | R5 | 2K8 | RESISTOR0805 | 805 | Generic Resistor Package
54 | P | IGUAL | P | MK1-JACK | 1 | R50 | 56K | RESISTOR0805 | 805 | Generic Resistor Package
55 | P | IGUAL | P | MK1-JACK | 1 | R51 | 390K | RESISTOR0805 | 805 | Generic Resistor Package
56 | P | IGUAL | P | DUAL-USBC | 2 | R55, R56 | 5K1 | RESISTOR0805 | 805 | Generic Resistor Package
57 | P | IGUAL | P | MK1-JACK | 1 | R57 | 800R | RESISTOR0805 | 805 | Generic Resistor Package
58 | P | IGUAL | P | MK1-JACK | 1 | R6 | 1K4 | RESISTOR0805 | 805 | Generic Resistor Package
59 | P | IGUAL | P | DUAL-USBC | 1 | R62 | 100K | RESISTOR0805 | 805 | Generic Resistor Package
60 | P | IGUAL | P | MK1-JACK | 1 | R7 | 180K | RESISTOR0805 | 805 | Generic Resistor Package
61 | P | IGUAL | P | MK1-JACK | 1 | R8 | 91K | RESISTOR0805 | 805 | Generic Resistor Package
62 | P | IGUAL | P | MK1-JACK | 1 | R9 | 43K | RESISTOR0805 | 805 | Generic Resistor Package
63 | P | IGUAL | P | MK1-JACK | 1 | R35 | 130R | RESISTOR0805 | 805 | Generic Resistor Package
64 | P | IGUAL | P | DUAL-USBC | 1 | RSENSE | 100mR | RESISTOR1206 | 1206 | Generic Resistor Package
65 | P | IGUAL | P | MK1-JACK | 1 | S1 | ROTARTY_ENCODER | ROTARTY_ENCODER | ROTARY_ENC_PLAIN | Simple no LED rotary encoder
66 | P | IGUAL | P | MK1-JACK | 1 | S2 |  | TAC_SWITCH_KSC931G-SMD | TAC_SW_SMD_KSC931G | Momentary Switch
67 | P | NUEVO | P | MK1-JACK | 1 | U1 | RP2040TR7 | RP2040TR7 | 56-QFN (7x7) | ARM MCU, RP2040 Series Microcontrollers, ARM Cortex-M0+, 32 bit, 133 MHz, 16 MB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 |  | https://www.digikey.es/es/products/detail/raspberry-pi/SC091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
